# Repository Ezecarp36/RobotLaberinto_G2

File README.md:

# RobotLaberinto_G2
Proyecto de robot laberinto para competir en la LNR 2023

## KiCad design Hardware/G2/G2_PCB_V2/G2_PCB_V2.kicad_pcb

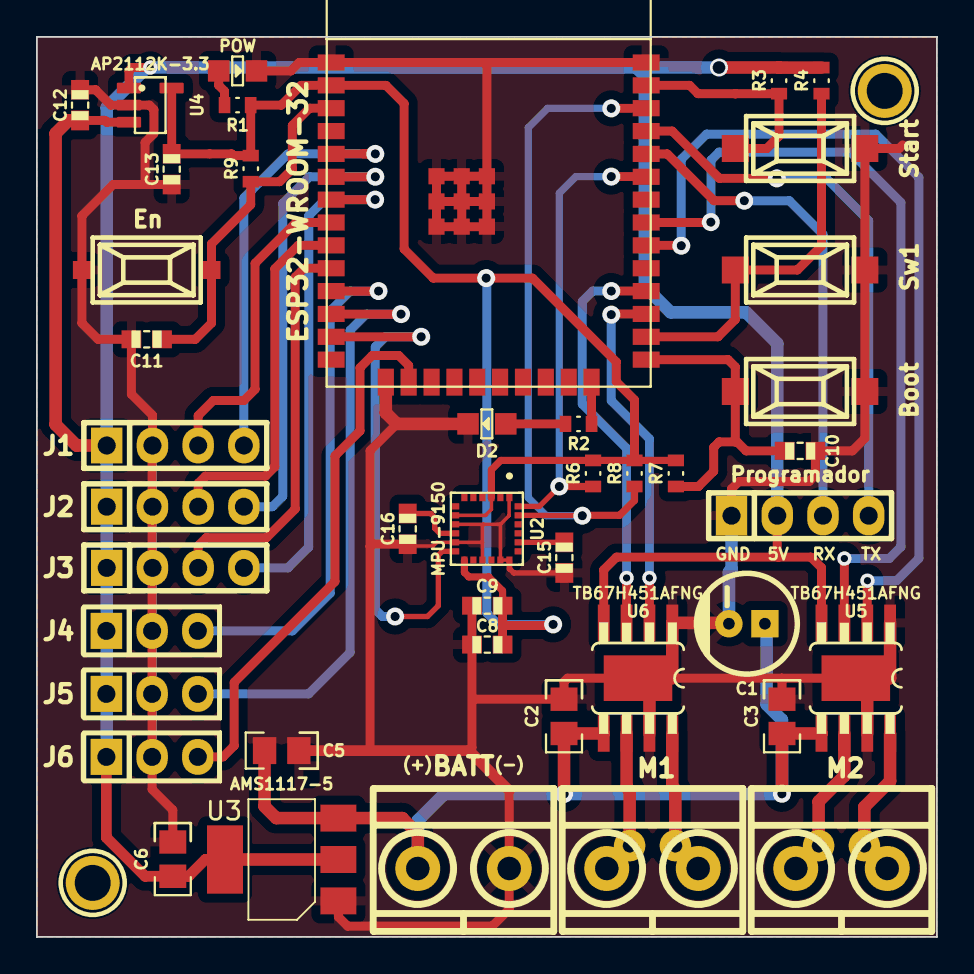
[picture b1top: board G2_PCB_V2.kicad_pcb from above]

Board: 2 copper layers, 50.0 x 50.0 mm, 45 parts (0 on the bottom side), 35 nets.

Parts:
BOOT1: SW_Push; Pulsador_SMD_2_ALTO
BORNERA2, BORNERA2#2: J**; BORNERA2_DUO
C1: 100Uf/30V; CAP_ELEC_5x11mm
C2, C3: 100nf; C_0805
C5: 100nF; C_0805
C6: 10uF; C_0805
C8, C12, C16: 100nF; C_0603
C9: 10nF; C_0603
C10, C11: 1n; C_0603
C13: 10uF; C_0603
C15: 2.2nF; C_0603
EN1: SW_Push; Pulsador_SMD_2_ALTO
H1, H2: Mounting_Hole; pad_3mm
J1: Sensor1; pin_strip_4
J2: Sensor2; pin_strip_4
J3: Sensor3; pin_strip_4
J4: Sensor4; Pin_Header_3
J5: Sensor5; Pin_Header_3
J6: Sensor6; Pin_Header_3
J8: BATT; BORNERA2_AZUL
LED1: POW; Led_0805
LED2: D2; Led_0805
Programador: J7; pin_strip_4
R1, R2: 1K; R_0603
R3, R4, R6, R7, R9: 10K; R_0603
R8: 1OK; R_0603
Star1: SW_Push; Pulsador_SMD_2_ALTO
Switch1: SW_Push; Pulsador_SMD_2_ALTO
U1: ESP32-WROOM-32
U2: MPU-9150; MPU-9150-Qfn-24
U3: AMS1117-5; SOT-223-3_TabPin2
U4: AP2112K-3.3; AP2112K-3.3-Sot25
U5, U6: TB67H451AFNG

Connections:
+3V3: C8.1, C9.1, C13.2, R1.1, R6.1, R7.1, R8.2, R9.2, U1.3V3, U2.3 (VDD), U2.8 (VLOGIC), U2.13 (VDD), U4.5 (VOUT)
+5V: C6.1, C12.1, J1.1, J2.1, J3.1, J4.1, J5.1, J6.1, Programador.2, R3.2, R4.2, U3.2 (VO), U4.1 (VIN), U4.3 (EN), U5.4 (VREF), U6.4 (VREF)
/BOTON_START: R3.1, Star1.2, U1.36 (IO23)
/BOTON_SWITCH_1: R4.1, Switch1.2, U1.24 (IO4)
/EN: C11.2, EN1.2, R9.1, U1.9 (EN)
/IN1_SENSOR: J1.4, U1.8 (SENSOR_VN)
/IN2_SENSOR: J2.4, U1.10 (IO34)
/IN3_SENSOR: J3.4, U1.11 (IO35)
/INT: U1.17 (IO14), U2.12 (INT)
/IN/OUT1: J4.3, U1.15 (IO26)
/IN/OUT2: J5.3, U1.16 (IO27)
/IN/OUT3: J6.3, U1.20 (IO13)
/IO0: BOOT1.2, C10.2, R8.1, U1.23 (IO0)
/IO2: R2.2, U1.22 (IO2)
/M1_IN1: U1.38 (IO19), U5.3 (IN1)
/M1_IN2: U1.35 (IO18), U5.2 (IN2)
/M2_IN1: U1.27 (IO17), U6.3 (IN1)
/M2_IN2: U1.25 (IO16), U6.2 (IN2)
/OUT1_SENSOR: J1.3, U1.12 (IO32)
/OUT2_SENSOR: J2.3, U1.13 (IO33)
/OUT3_SENSOR: J3.3, U1.14 (IO25)
/OUT_A_M1: BORNERA2#2.2, U5.8 (OUT2)
/OUT_A_M2: BORNERA2.2, U6.8 (OUT2)
/OUT_B_M1: BORNERA2#2.1, U5.6 (OUT1)
/OUT_B_M2: BORNERA2.1, U6.6 (OUT1)
/RXD0: Programador.3, U1.40 (RXD0)
/SCL: R7.2, U1.39 (IO22), U2.23 (SCL)
/SDA: R6.2, U1.42 (IO21), U2.24 (SDA)
/TXD0: Programador.4, U1.41 (TXD0)
GND: BOOT1.1, C1.2, C2.2, C3.2, C5.2, C6.2, C8.2, C9.2, C10.1, C11.1, C12.2, C13.1, C15.1, C16.1, EN1.1, J1.2, J2.2, J3.2, J4.2, J5.2, J6.2, J8.2, LED1.2 (K), LED2.2 (K), Programador.1, Star1.1, Switch1.1, U1.GND, U2.1 (CLKIN), U2.9 (AD0), U2.11 (FSYNC), U2.15 (GND), U2.17 (GND), U2.18 (GND), U3.1 (GND), U4.2 (GND), U5.1 (GND), U5.7 (RS), U6.1 (GND), U6.7 (RS)
unnamed: LED1.1 (A), R1.2
unnamed: LED2.1 (A), R2.1
unnamed: C15.2, U2.20 (CPOUT)
unnamed: C16.2, U2.10 (REGOUT)
VCC: C1.1, C2.1, C3.1, C5.1, J8.1, U3.3 (VI), U5.5 (VM), U6.5 (VM)

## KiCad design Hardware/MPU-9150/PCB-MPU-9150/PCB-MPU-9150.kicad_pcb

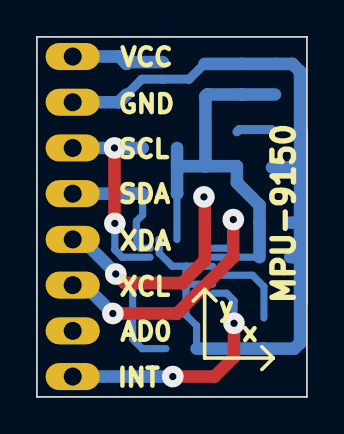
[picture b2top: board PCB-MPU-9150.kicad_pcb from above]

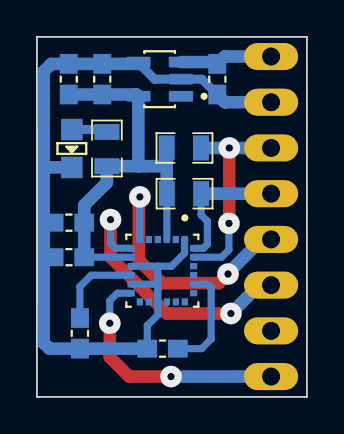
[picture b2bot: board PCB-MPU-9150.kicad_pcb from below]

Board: 2 copper layers, 15.0 x 20.0 mm, 14 parts (13 on the bottom side), 11 nets.

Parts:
C1: 2.2nF; C_0603
C2, C3, C5: 100nF; C_0603
C4: 10nF; C_0603
C6: 10uF; C_0603
C7: 4.7uF; C_0603
LED1: LED; Led_0805
P1: CONN_01X08; GY-521-MPU-6050
R1, R2: 10K; R_0805
R3: 1K; R_0805
U1: MPU-9150; MPU-9150-Qfn-24
U2: AP2112K-3.3; AP2112K-3.3-Sot25

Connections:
+3.3V: C3.1, C4.1, C5.2, C6.2, R1.1, R2.1, R3.1, U1.3 (VDD), U1.8 (VLOGIC), U2.5 (VOUT)
/INT: P1.8, U1.12 (INT)
/SCL: P1.3, R2.2, U1.23 (SCL)
/SDA: P1.4, R1.2, U1.24 (SDA)
/XCL: P1.6, U1.7 (ES_CL)
/XDA: P1.5, U1.6 (ES_DA)
GND: C1.1, C2.1, C3.2, C4.2, C5.1, C6.1, C7.2, LED1.2 (K), P1.2, U1.1 (CLKIN), U1.9 (AD0), U1.11 (FSYNC), U1.15 (GND), U2.2 (GND)
unnamed: LED1.1 (A), R3.2
unnamed: C1.2, U1.20 (CPOUT)
unnamed: C2.2, U1.10 (REGOUT)
VCC: C7.1, P1.1, U2.3 (EN)

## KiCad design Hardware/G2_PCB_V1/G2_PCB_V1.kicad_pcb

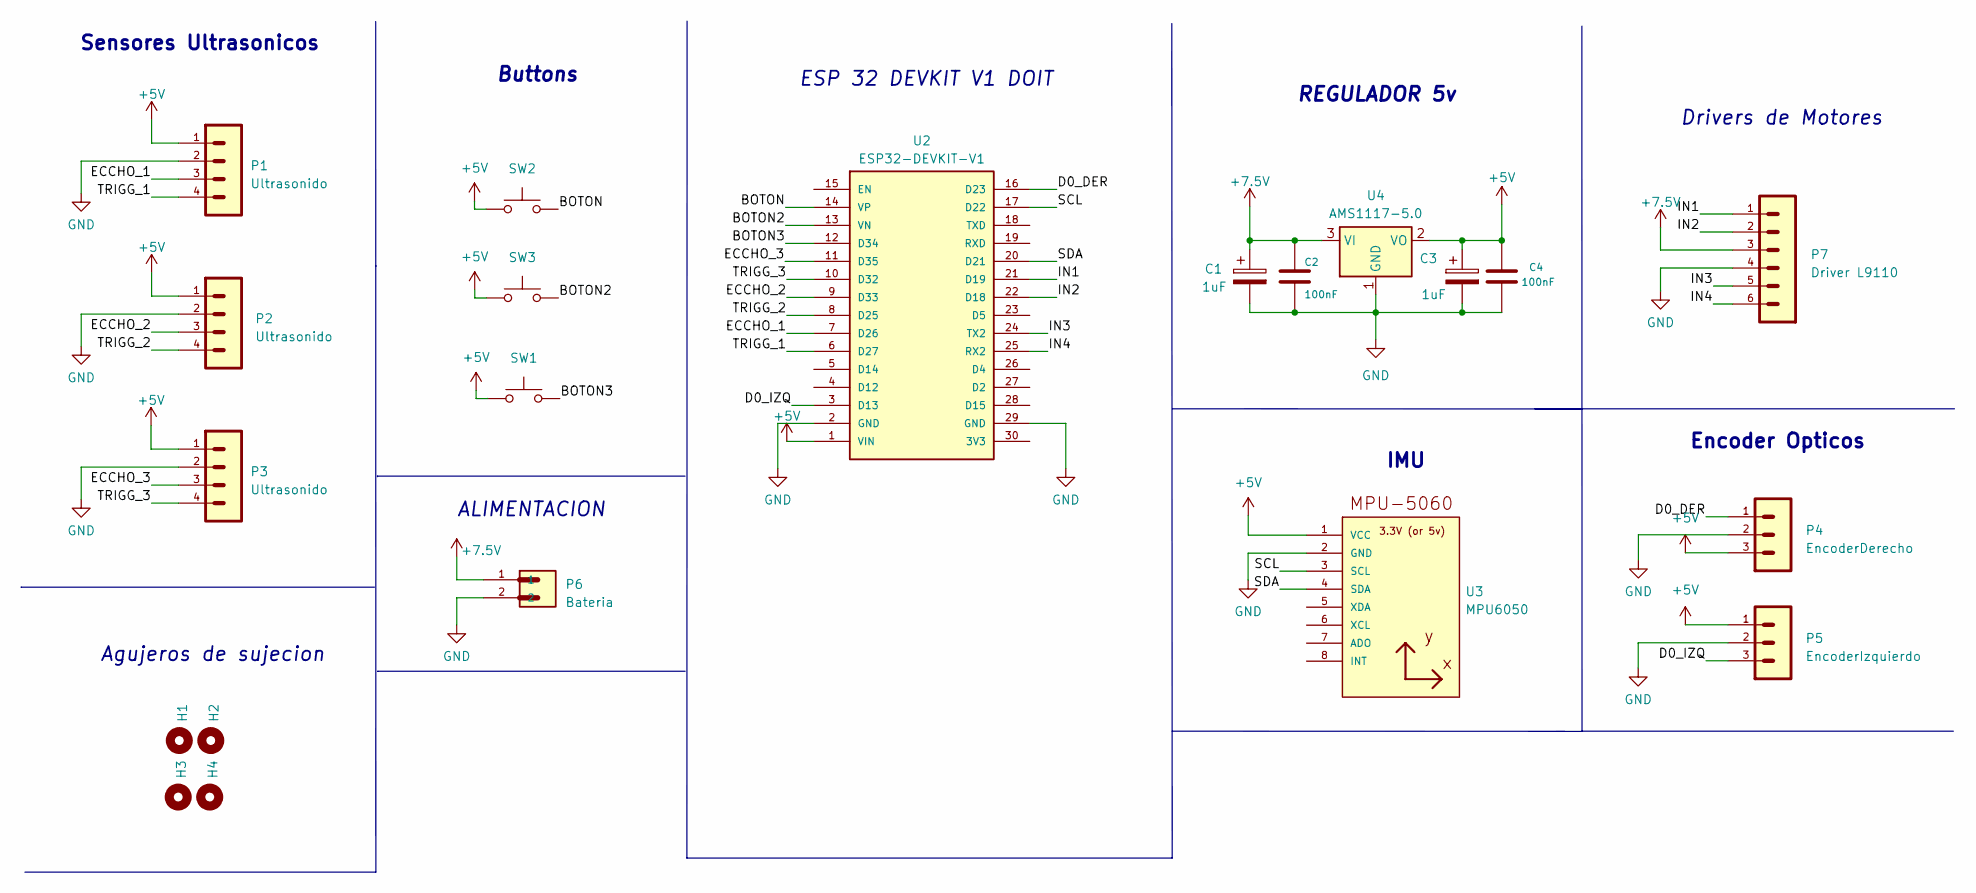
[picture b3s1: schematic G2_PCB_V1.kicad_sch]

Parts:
C1, C3: 1uF; C_0805
C2, C4: 100nF; C_0805
H1, H2, H3, H4: Mounting_Hole; hole_3mm
P1, P2, P3: Ultrasonido; JstXH4P
P4: EncoderDerecho; JstXH3P
P5: EncoderIzquierdo; JstXH3P
P6: Bateria; BORNERA2_AZUL
P7: Driver L9110; JstXH6P
SW1, SW2, SW3: SW_Push; Pin_Header_2
U2: ESP32-DEVKIT-V1; ESP32-DEVKIT-V1-30Pines
U3: MPU6050; MPU-6050
U4: AMS1117-5.0; SOT-223-3_TabPin2

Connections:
+5V: C3.1, C4.1, P1.1, P2.1, P3.1, P4.3, P5.1, SW1.1, SW2.1, SW3.1, U2.1 (VIN), U3.1 (VCC), U4.2 (VO)
+7.5V: C1.1, C2.1, P6.1, P7.3, U4.3 (VI)
/BOTON: SW2.2, U2.14 (VP)
/BOTON2: SW3.2, U2.13 (VN)
/BOTON3: SW1.2, U2.12 (D34)
/D0_DER: P4.1, U2.16 (D23)
/D0_IZQ: P5.3, U2.3 (D13)
/ECCHO_1: P1.3, U2.7 (D26)
/ECCHO_2: P2.3, U2.9 (D33)
/ECCHO_3: P3.3, U2.11 (D35)
/IN1: P7.1, U2.21 (D19)
/IN2: P7.2, U2.22 (D18)
/IN3: P7.5, U2.24 (TX2)
/IN4: P7.6, U2.25 (RX2)
/SCL: U2.17 (D22), U3.3 (SCL)
/SDA: U2.20 (D21), U3.4 (SDA)
/TRIGG_1: P1.4, U2.6 (D27)
/TRIGG_2: P2.4, U2.8 (D25)
/TRIGG_3: P3.4, U2.10 (D32)
GND: C1.2, C2.2, C3.2, C4.2, P1.2, P2.2, P3.2, P4.2, P5.2, P6.2, P7.4, U2.2 (GND), U2.29 (GND), U3.2 (GND), U4.1 (GND)

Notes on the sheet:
IMU
Encoder Opticos
Agujeros de sujecion
Sensores Ultrasonicos
Drivers de Motores
Buttons
ALIMENTACION
REGULADOR 5v
ESP 32 DEVKIT V1 DOIT

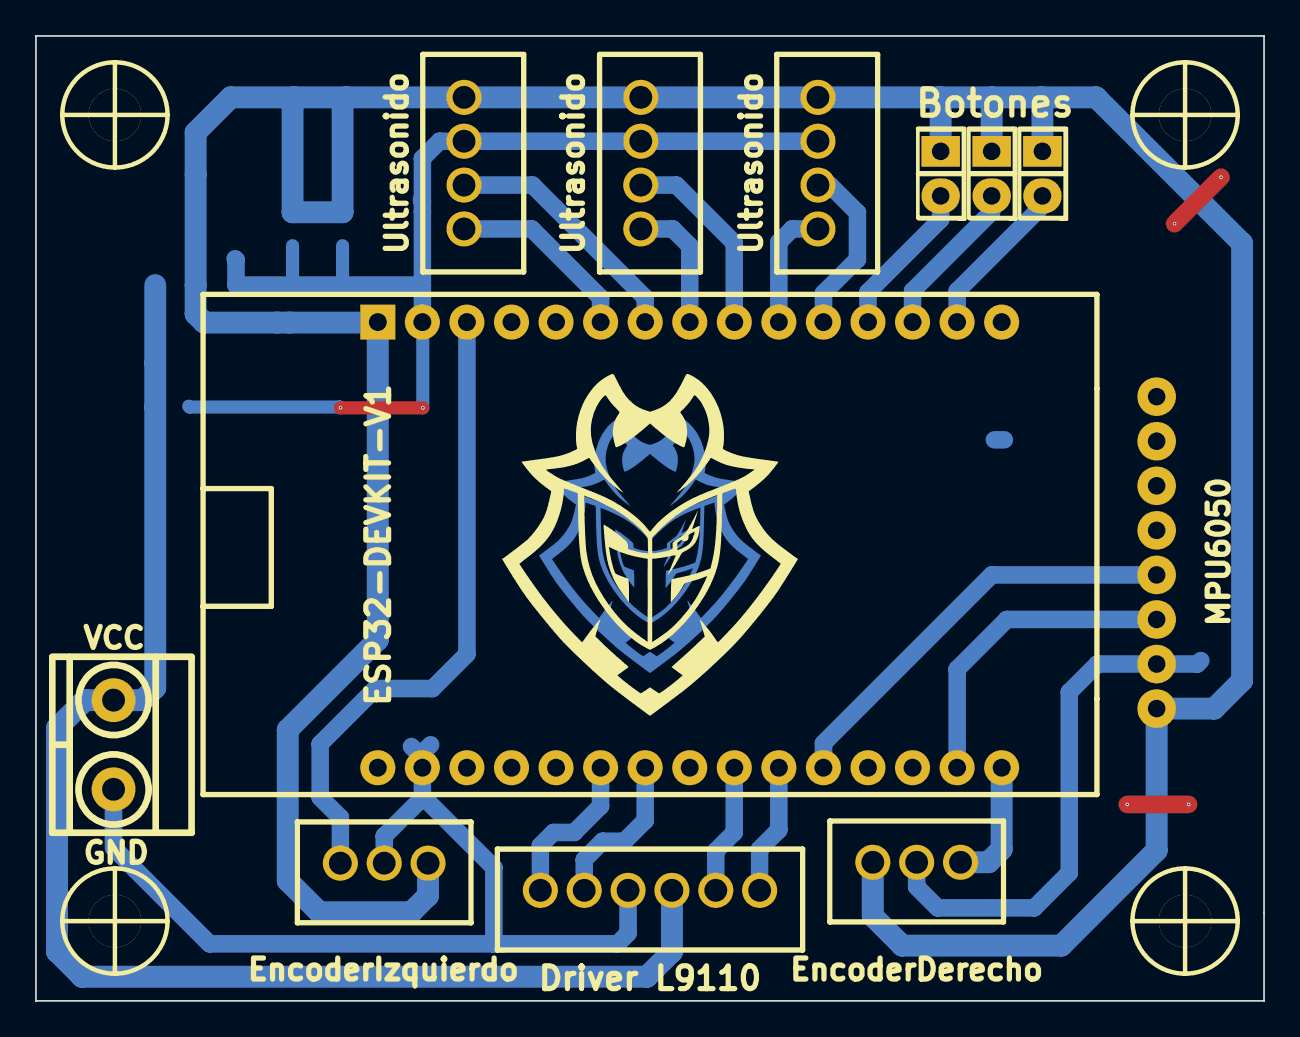
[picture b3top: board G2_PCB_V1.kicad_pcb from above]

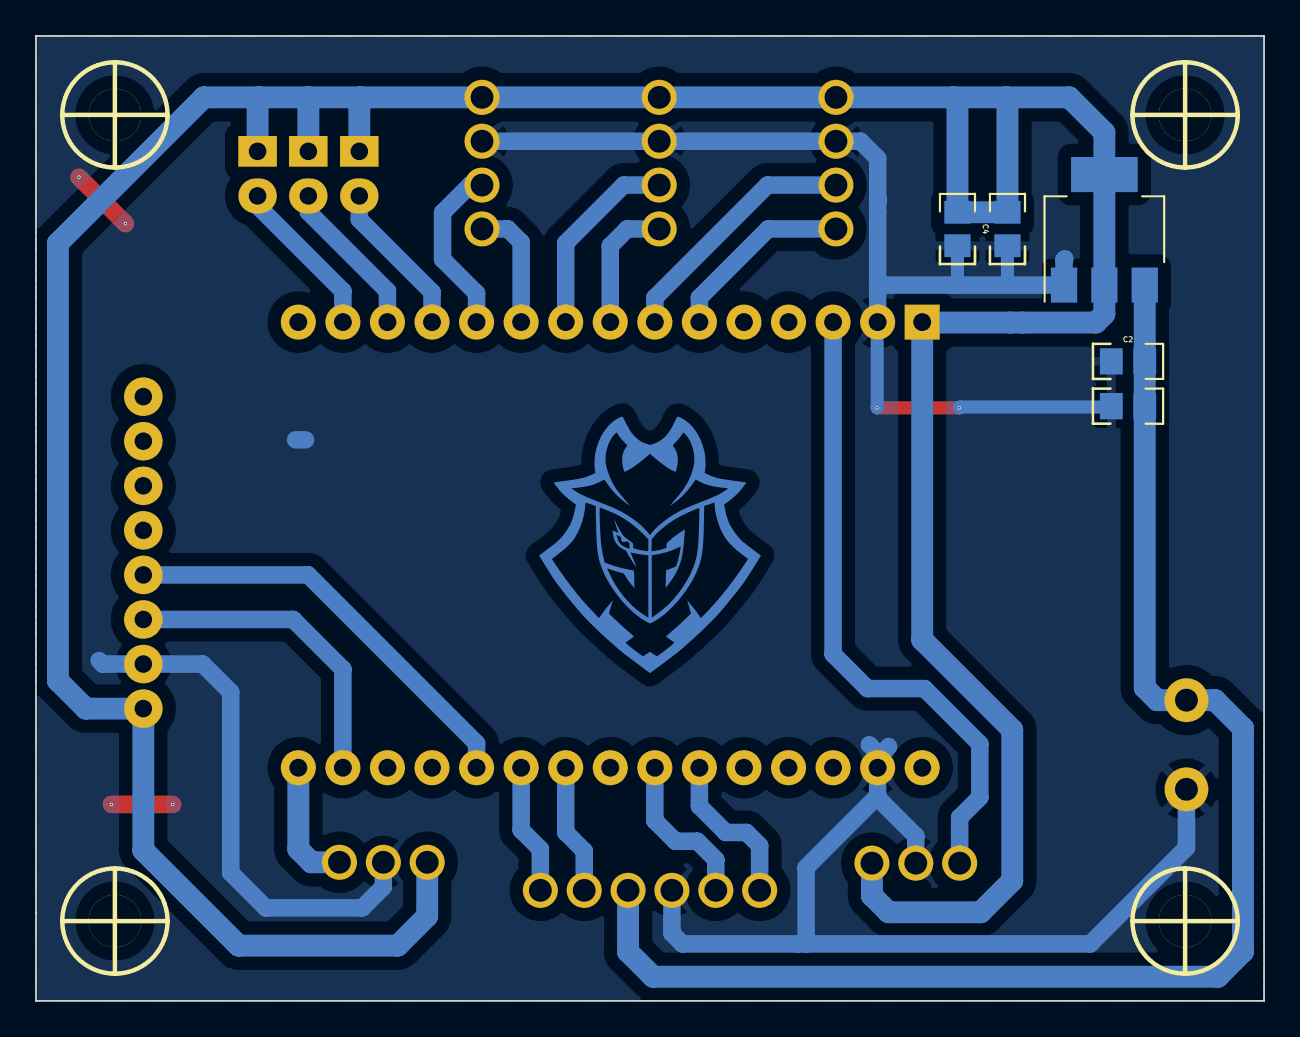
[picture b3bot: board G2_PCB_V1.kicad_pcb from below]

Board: 2 copper layers, 70.0 x 55.0 mm, 21 parts (5 on the bottom side), 20 nets.

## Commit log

2023-06-09 PCB de G2 version 1 terminado
2023-07-25 comence a desarrollar un modulo para la mpu9150, PCB terminado listo para fabricar y probar su funcionamiento
2023-08-04 empece el nuevo diseño para el robot laberinto G2
2023-08-26 agregue la version final de la mpu9150 y la version final del Pla version 2 del PCB
2023-11-03 agregue el codigo de laberinto
2023-11-03 Agregue los modelos 3D
2025-05-04 Agregue a mi liberia de sensores la clase del sensor laser VL53L0X y cree un codigo de ejemplo de su uso en la carpeta examples de la libreria
2025-05-05 agregue el codigo de prueba de los sensores VL53L0X en el robot y modifique el codigo de prueba del PID para poder usarlo con dichos sensores
2025-05-06 fix sensor init functions
2025-05-17 Fix error in DistanceSensors
2025-05-17 feat: code for new ledc library in 3.0.0
2025-05-17 fix: error if empty
2025-05-21 Cambios en PruebaVL53L0X.ino
2025-05-24 init platformio laberinto
2025-05-25 Add utils. Sensors working
